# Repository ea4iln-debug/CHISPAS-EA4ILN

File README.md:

# Chispas EA4ILN

**Entrenador de telegrafía (CW) portátil para radioaficionados, basado en la Heltec WiFi LoRa 32 V3.**

> *"Chispas"* era el apodo que se daba al radiotelegrafista de a bordo.

> [!WARNING]
> **Desde la v1.10 Chispas ya no es beta**, pero sigue siendo un proyecto personal montado en placa perforada: la
> salida KEY se ha probado con dos transceptores y algunos valores del circuito son de partida. Úsalo bajo tu
> responsabilidad: lee el [descargo de responsabilidad](#descargo-de-responsabilidad).

<p align="center">
  
  <br>
  <sub>El prototipo en protoboard (12 de octubre de 2026): Heltec V3 con antena LoRa, encoder, buzzer, volumen,
  manipulador de palas, jacks de auriculares, de KEY y de audio de la emisora, optoacoplador y sensor BME280.</sub>
</p>

Chispas reúne en un aparato de bolsillo lo necesario para aprender y practicar CW: un entrenador por el método Koch,
un keyer iámbico, un modo de repetición (Echo), práctica en pareja y QSO por radio LoRa, conexión con el transceptor
(manipulación por KEY, tune, decodificador y memorias) y utilidades de estación, como la propagación, los spots POTA y
la línea gris. Todo se maneja con un encoder rotativo y una pantalla OLED, y se actualiza solo desde las releases de
GitHub.

---

## Índice

- [Funciones](#funciones)
- [Hardware](#hardware)
- [Conexiones](#conexiones)
- [Instalar el firmware](#instalar-el-firmware)
- [Actualizar por WiFi (OTA)](#actualizar-por-wifi-ota)
- [Manejo](#manejo)
- [Pantallas](#pantallas)
- [Configuración](#configuración)
- [Estructura del repositorio](#estructura-del-repositorio)
- [Detalles técnicos](#detalles-técnicos)
- [Hoja de ruta](#hoja-de-ruta)
- [Avisos](#avisos)
- [Descargo de responsabilidad](#descargo-de-responsabilidad)
- [Créditos y referencias](#créditos-y-referencias)
- [Licencia](#licencia)
- [Autor](#autor)

---

## Funciones

| Función | Descripción | Estado |
|---|---|---|
| **Koch (RX)** | Orden de caracteres de LCWO (lecciones 1–40), grupos aleatorios configurables (wpm, velocidad efectiva como en LCWO, caracteres y grupos), o **indicativos** al azar y **frases de QSO POTA**. La letra nueva de cada lección sale el 25 % de las veces y, con el **refuerzo**, las letras que más fallas salen más (hasta el doble o el triple). Al terminar se corrige **letra a letra** (marcando cada fallo) o con el **total de fallos**; estadísticas por lección y por carácter. | ✅ |
| **Echo (TX)** | Chispas emite letras y hay que repetirlas con las palas. Ajustes propios (wpm, velocidad efectiva, lección, letras por reto, número de retos, refuerzo de las letras con más errores), resultado al terminar y estadísticas por lección y por carácter. | ✅ |
| **TX libre (keyer iámbico)** | Modos A y B, 10–40 wpm, palas normales o invertidas. Descodifica en pantalla lo que se manipula y mide tu **ritmo** (espacios entre letras y palabras, titubeos, velocidad real) con un consejo. | ✅ |
| **QSO SIM** | Simulador de QSO POTA con las palas, en los dos papeles (ajuste **ROL**): de cazador (Chispas llama CQ; tú, indicativo, `5NN`, `73`) o de activador (llamas tú CQ y Chispas es el cazador: a veces da medio indicativo, vuelve a llamar si tardas o copia mal el tuyo). Si no te copia, te pide repetir. Velocidad y velocidad efectiva del activador, texto en pantalla y condiciones de banda: **QSB**, **ruido**, **estática de tormenta** y **QRM** (NO / SUAVE / FUERTE). | ✅ |
| **Práctica Duo por LoRa** | Práctica en pareja entre dos Chispas: uno envía grupos (o indicativos, o frases de QSO POTA) y el otro los recibe y los copia. Tramas digitales a 868 MHz, sin audio. | ✅ |
| **QSO libre por LoRa** | QSO con las palas entre dos Chispas: cada palabra se envía al terminarla y lo recibido suena cuando dejas de manipular (si manipulas mientras suena, se corta). | ✅ |
| **Transceptor (TRX)** | Manipulación de la emisora por KEY (aislada con optoacoplador), **tune** (portadora de 1–10 s), 6 memorias con variables (`{MI}`, `{SU}`, `{WX}`), decodificador CW del audio de la emisora (comprobado con audio Morse real) y QSO con las dos cosas a la vez (OPERAR para copiar de oído; QSO para que CHISPAS decodifique mientras transmites). | ✅ |
| **Propagación** | Índices solares y condiciones por banda de [hamqsl.com](https://www.hamqsl.com/). | ✅ |
| **Spots POTA** | Activaciones en CW publicadas en [pota.app](https://pota.app/). **Autospot** (beta): desde los parques cercanos, publicas tu propio spot (parque, indicativo, banda, frecuencia, QRP/QRT o un comentario propio) y CHISPAS te avisa a los 25 min para renovarlo. La **activación en curso** (duración, spots, botón de QRT) no se olvida aunque apagues. | ✅ |
| **Cluster** (beta) | Spots en vivo por telnet: el [RBN](https://reversebeacon.net/) (receptores automáticos de CW, con dB y WPM), el cluster de la [URE](https://www.ure.es/cluster-telnet-ea4ure/) (`ea4ure.com:7300`), VE7CC, WA9PIE o uno propio desde WEBCONF. Filtros de modo (TODOS/CW) y banda en CHISPAS, nunca en tu cuenta del cluster. Un spot por estación, con el mejor receptor y cuántos la oyen; "a SU" pasa su indicativo a TRX. **¿Quién me oye?**: los receptores del RBN que copian tu CQ, con la distancia exacta a cada uno; con **ESCUCHA EN TRX** (SI de serie) sigue escuchando el RBN mientras llamas CQ desde TRX › OPERAR o QSO (solo ahí se enciende el WiFi), y su `menu` lleva directo a la lista (y vuelve). | ✅ |
| **Sol y línea gris** | Salida y puesta del sol y ventanas de línea gris de hoy y de mañana, y altura actual del sol, para el locator de la estación. Funciona sin conexión. | ✅ |
| **Sensor ambiental (BME280)** | Temperatura, humedad y presión; tendencia de la presión en 3 h con **aviso de tormenta**; altitud barométrica calibrable (útil en SOTA); la temperatura en las memorias con `{WX}`. Opcional: sin sensor, Chispas funciona igual. | ✅ |
| **Configuración en el aparato** | Indicativo, locator, altitud, aceleración del encoder, apagado automático, tono y reset de fábrica, con el encoder. Página STATUS con estación, sistema, WiFi, memoria, arranque y sensor. | ✅ |
| **Configuración por WiFi** | Portal web en castellano, con QR para unirse desde el móvil: red, estación, hora y memorias. | ✅ |
| **Actualización OTA** | Busca la última release en GitHub, avisa si hay versión nueva y la instala por WiFi (TLS validado). | ✅ |
| **Batería** | Tensión y porcentaje. Detecta cuando no hay batería conectada. | ✅ |
| **Cara de Chispas** | Salvapantallas animado con expresiones y gestos, también de radioaficionado: antena llamando CQ, auriculares, bocadillo con CQ/73/88 y guiño en Morse. Reacciona a la línea gris, a la buena propagación y al aviso de tormenta. Sale tras el tiempo elegido sin uso en cualquier pantalla salvo CW, LoRa y TRX. | ✅ |
| **Tono por altavoz y auriculares** | Tono CW (400–1000 Hz, 850 por defecto) por un altavoz con amplificador PAM8302A, con volumen y silencio automático del altavoz al conectar auriculares. Audio sintetizado (sigma-delta a 16 kHz): tono sin clics y, en el simulador, ruido, estática, QRM y QSB. El amplificador solo se enciende en CW, LoRa y TRX. | ✅ |
| **Ahorro de energía** | CPU a 80 MHz sin WiFi, radio dormida fuera de LoRa, pantalla atenuada y apagado automático (deep sleep). | ✅ |
| **GPS** | Hora, locator y altitud automáticos (QNH del BME280 e historial de presión a nivel del mar). Duerme casi siempre para ahorrar. Opcional. | ✅ |

---

## Hardware

Resumen con fotos, fases del desarrollo, piezas, conexiones y la PCB (aún sin probar):
**[página de hardware](https://ea4iln-debug.github.io/CHISPAS-EA4ILN/hardware.html)**.

### Placa principal
- **[Heltec WiFi LoRa 32 V3](https://heltec.org/project/wifi-lora-32-v3/)**: ESP32-S3FN8 (8 MB de flash, sin PSRAM), radio
  LoRa SX1262 a 868 MHz, pantalla OLED de 0,96" (128×64, SSD1306) y cargador de batería LiPo integrado.

### Componentes del prototipo
El prototipo actual se monta en protoboard, sin PCB. Componentes principales:

- Encoder rotativo **KY-040** con pulsador.
- Manipulador de **palas** con clavija estéreo de 3,5 mm.
- Amplificador **PAM8302A** con **altavoz de 8 Ω**, potenciómetro de volumen de 10 kΩ logarítmico y jack de
  auriculares con conmutación (al meter la clavija, el altavoz calla). Sustituye al buzzer piezoeléctrico del
  principio, que a 3,3 V sonaba muy bajo.
- Optoacoplador **PC817** para la salida KEY, con resistencia de 10 kΩ a GND y un jack con la punta y el anillo
  unidos (vale para emisoras que manipulan por cualquiera de los dos).
- Entrada de audio de la emisora para el decodificador: polarización a 1,65 V, trimmer de nivel y diodos de protección.
- Módulo **GPS** NEO-6M (opcional): hora, locator y altitud. Se duerme por software entre lecturas.
- Batería **LiPo** de 3,7 V con conector JST de 1,25 mm. Comprueba la polaridad antes de conectarla.

El esquema completo (7 hojas), con la lista de componentes y el orden de montaje, está en
[`docs/esquema_protoboard.pdf`](docs/esquema_protoboard.pdf).

---

## Conexiones

| GPIO | Conector | Uso | Estado |
|---|---|---|---|
| 2 | J3-13 | Salida KEY (PC817, 330 Ω, y 10 kΩ a GND). Solo la activa la pantalla TRX | ✅ (probada con una uSDR y una Xiegu X6200) |
| 4 | J3-15 | Pala de punto (DIT), pull-up interno | ✅ |
| 5 | J3-16 | Pala de raya (DAH), pull-up interno | ✅ |
| 6 | J3-17 | Entrada de audio del decodificador (ADC1, por DMA) | ✅ |
| 7 | J3-18 | Tono CW por sigma-delta (amplificador con altavoz y auriculares) | ✅ |
| 38 | J3-11 | Apagado (SD) del amplificador PAM8302A: solo encendido en CW, LoRa y TRX | ✅ |
| 19 | J2-18 | Encoder CLK | ✅ |
| 20 | J2-17 | Pulsador del encoder (también despierta la placa) | ✅ |
| 48 | J2-14 | Encoder DT | ✅ |
| 47 | J2-13 | RX desde el TX del GPS | ✅ |
| 39 | J3-10 | TX al RX del GPS (órdenes UBX para dormirlo) | ✅ |
| 41 / 42 | J3-8 / J3-7 | I2C (Wire1) del sensor BME280 (opcional) | ✅ |

Notas:
- El pin 1 de cada conector es el de pad cuadrado, el más cercano al USB, y es GND. La alimentación de 3,3 V está en J3-2/3.
- Todos los módulos van a **3,3 V**. Los GPIO del ESP32-S3 no admiten 5 V.
- GPIO19 y GPIO20 son las líneas USB D−/D+ del S3, pero funcionan como entradas porque la V3 programa a través de un
  conversor CP2102 (probado en placa). En Windows hace falta el driver
  [CP210x de Silicon Labs](https://www.silabs.com/developers/usb-to-uart-bridge-vcp-drivers).

---

## Instalar el firmware

El firmware es para la placa con **encoder**. Hasta la v1.10 hubo también una compilación `sin-encoder`, para una
placa desnuda que se manejaba solo con el botón PRG; desde la 1.20 ya no existe (una placa sin encoder se queda en la
v1.10; el OTA dirá que no hay binario para ella).

### Desde el navegador (lo más fácil)
Abre **[ea4iln-debug.github.io/CHISPAS-EA4ILN](https://ea4iln-debug.github.io/CHISPAS-EA4ILN/)** con Chrome o Edge
en un ordenador, conecta la placa por USB y pulsa **Instalar en la placa**. Instala la última versión estable o,
si hay una más nueva, la **beta** (selector encima del botón), y **conserva la configuración** guardada, salvo que marques borrar la placa (recomendable si traía otro firmware).
En Windows hace falta el driver del CP210x (ver arriba).

### Sin compilar (desde la release)
En [Releases](https://github.com/ea4iln-debug/CHISPAS-EA4ILN/releases) están las imágenes listas:

| Archivo | Para qué |
|---|---|
| `chispas-<versión>-usb.bin` | Primera instalación por USB (imagen completa, se graba en `0x0`) |
| `chispas-<versión>.bin` | Solo la aplicación: la usa la actualización OTA |

Para grabar la imagen completa basta con [ESP Tool web](https://espressif.github.io/esptool-js/) (en Chrome o Edge:
*Connect*, dirección `0x0`, el archivo `-usb.bin` y *Program*) o, con Python:

```bash
pip install esptool
esptool.py --chip esp32s3 --port COMx write_flash 0x0 chispas-1.03b-usb.bin
```

La imagen completa **borra la configuración** guardada (estación, estadísticas y red WiFi): úsala para la primera
instalación. Para las siguientes versiones, usa la [actualización por WiFi](#actualizar-por-wifi-ota), que lo conserva.

### Compilando (PlatformIO)
- [Visual Studio Code](https://code.visualstudio.com/) con la extensión [PlatformIO IDE](https://platformio.org/), o
  la línea de órdenes de PlatformIO (`pio`).
- Cable USB-C con datos.

Las dependencias se instalan solas al compilar. Están fijadas en [`platformio.ini`](platformio.ini):

| Componente | Versión |
|---|---|
| Plataforma `espressif32` (core Arduino 2.0.17) | 6.13.0 |
| [RadioLib](https://github.com/jgromes/RadioLib) | ^6.6 |
| [Adafruit GFX](https://github.com/adafruit/Adafruit-GFX-Library) y [SSD1306](https://github.com/adafruit/Adafruit_SSD1306) | ^1.11 / ^2.5 |
| [WiFiManager](https://github.com/tzapu/WiFiManager) | ^2.0.17 |
| [ArduinoJson](https://arduinojson.org/) | ^7.2 |

```bash
git clone https://github.com/ea4iln-debug/CHISPAS-EA4ILN.git
cd CHISPAS-EA4ILN
pio run                                         # compila el firmware
pio run -t upload --upload-port COMx            # lo carga (en Linux/macOS, /dev/ttyUSB0 o similar)
pio device monitor                              # monitor serie a 115200 baudios
```

### Programas de prueba
En [`pruebas/`](pruebas/) hay programas independientes para comprobar el hardware sin tocar el firmware:

| Entorno | Para qué |
|---|---|
| `pio run -e prueba_pines -t upload` | Comprueba los pines del encoder e imprime por serie cada cambio y el sentido de giro |
| `pio run -e prueba_bateria -t upload` | Mide la lectura de batería (media y dispersión) con y sin batería conectada |

Después de usarlos, vuelve a cargar el firmware con `pio run -t upload`.

---

## Actualizar por WiFi (OTA)

Con una red WiFi guardada (ver [Configuración](#configuración)):

1. Ve a **CONF. > CONFIG > ACTUALIZAR FW**. Chispas se conecta, consulta la última release de este repositorio
   (también las beta) y la compara con la instalada.
2. Si hay una más nueva, la enseña (`NUEVA v1.01b`) y pide confirmar con **instalar**. Descarga el binario de su
   placa, lo instala en la otra partición de la flash y reinicia. Si algo falla, la versión
   instalada sigue intacta.
3. Además, cuando Chispas enciende el WiFi en PROP. o POTA, mira una vez al día si hay versión nueva y lo
   avisa en el menú (`FW NUEVO: v1.01b`).
4. Si la descarga se queda parada 30 s, Chispas se reinicia y sigue con la versión que tenía.

Con batería por debajo del 30 % (y sin USB) no instala, para que no se quede a medias. La conexión con GitHub va
cifrada y se comprueba con los certificados raíz de [`include/certificados_github.h`](include/certificados_github.h).

---

## Manejo

Todo se hace con el **encoder**:

| Acción | Efecto |
|---|---|
| **Girar** | Mueve el foco por las opciones, incluidas las flechas `ant.` y `sig.` para cambiar de pantalla; en las páginas de datos, pasa de página |
| **Pulsar** | Ejecuta la opción con el foco |
| **Pulsar sobre un valor** | Entra en edición (el valor sale en vídeo inverso): girar lo cambia y pulsar otra vez lo confirma. Al girar rápido, los valores largos avanzan de varios en varios (aceleración, ajustable en CONFIG) |
| **Pulsación larga** | Atajo en algunas pantallas, como salir de la práctica o repetir |
| **Botón PRG** (corto) | *Atrás*: sale de la edición o del submenú y, en las pantallas principales, vuelve a Inicio |
| **Botón PRG** (largo) | Duerme Chispas (deep sleep); se despierta pulsando PRG o el eje del encoder |

Todas las pantallas siguen el mismo esquema:
- **Menú:** título en negativo, opciones `< ... >` y `ant.`/`sig.` abajo.
- **Ajustes:** lista con el nombre a la izquierda y el valor a la derecha (4 a la vista, con barra de desplazamiento),
  y las acciones en el pie (`volver`, o `iniciar` y `volver`).
- **Datos en páginas:** se pasan girando; el pie dice la página (`1/2 INDICES`) y pulsar vuelve.
- **Pantallas de manipular o escuchar** (TX libre, Operar, QSO, Duo, Decodificar): pie corto con lo que se usa sin
  soltar las palas y **menu** para el resto de ajustes.

Al cambiar de pantalla, el foco se queda en la flecha que has usado, así que basta con pulsar varias veces seguidas
para recorrer las pantallas en un sentido.

Sin encoder (compilación `sin-encoder`, solo hasta la v1.10), todo se hace con el botón PRG: corta = mover el foco, larga = ejecutar y
muy larga (2,5 s) = dormir.

---

## Pantallas

| N.º | Pantalla | Contenido |
|---|---|---|
| 1 | **Inicio** | Nombre, indicativo y versión. Tras unos segundos sin uso aparece la cara de Chispas (también en PROP., POTA, SOL, TIEMPO y CONF.). |
| 2 | **CW** | Entrenador: `KOCH (RX)`, `ECHO (TX)`, `QSO SIM` (simulador de QSO POTA) y `tx libre` en el pie (keyer), con ajustes, práctica y estadísticas |
| 3 | **LoRa** | `PRÁCTICA DUO` (grupos en pareja) y `QSO LIBRE` (con las palas) |
| 4 | **TRX** | Transceptor: `DECODIFICAR` (solo recibe), `OPERAR` (transmitir por KEY, con memorias y tune, copiando de oído), `QSO` (OPERAR con el decodificador a la vez) y `memorias` |
| 5 | **PROP.** | Propagación: índices solares y condiciones por banda |
| 6 | **POTA** | Spots de activaciones en CW, parques POTA más cercanos (con el GPS o el locator) y autospot desde un parque |
| 7 | **CLUSTER** (`DXC` en la cabecera) | Spots en vivo por telnet del RBN (por defecto), del cluster de la URE u otros, con filtros de modo y banda; ficha del spot y "a SU" (pasa el indicativo a TRX); `QUIÉN ME OYE?`: los receptores del RBN que te copian, del más lejano al más cercano, con km y dB. Necesita tu indicativo y WiFi |
| 8 | **SOL** | Sol y línea gris: hoy, ahora y mañana |
| 9 | **TIEMPO** (`WX` en la cabecera) | Tiempo de [Open-Meteo](https://open-meteo.com/) (CC BY 4.0) para el locator o el GPS: ahora, próximas 12 h cada 3 h y mañana; con el BME280, también AMBIENTE |
| 10 | **CONF.** | `CONFIG` (estación, encoder, apagado, tono, webconf, actualización, depuración y fábrica) y `STATUS` |

La cabecera muestra la hora (local o UTC, a elegir), una `W` si el WiFi está encendido y una `L` si la radio LoRa
está escuchando (Práctica Duo y QSO libre), ambas en negativo, el nombre de la pantalla y la batería (`PWR` si no hay
batería).
Las capturas salen de la propia pantalla con [`docs/captura_oled.py`](docs/captura_oled.py) (necesita
**CONF. > CONFIG > DEPURACION > ORDENES SERIE** en `SI`).

### Entrenador CW

| | | |
|:---:|:---:|:---:|
| <br>Menú | <br>Koch: ajustes | <br>Koch: práctica |
| <br>Koch: grupos emitidos | <br>Koch: corregir con el total | <br>Koch: más errores |
| <br>Koch: totales | <br>Koch: lecciones | <br>Echo: ajustes |
| <br>Echo: práctica | <br>Echo: más errores | <br>Echo: lecciones |
| <br>TX libre (keyer) | <br>TX libre: menu | <br>QSO SIM: ajustes |

### LoRa

| | | |
|:---:|:---:|:---:|
| <br>Menú | <br>Práctica Duo | <br>Duo: menu |
| <br>QSO libre | <br>QSO libre: menu | |

### Transceptor (TRX)

| | | |
|:---:|:---:|:---:|
| <br>Menú | <br>Operar | <br>Operar y QSO: menu |
| <br>QSO | <br>Decodificar (sin señal) | <br>Memorias |
| <br>Editor (rueda de caracteres, con {WX}) | | |

### Cluster

| | | |
|:---:|:---:|:---:|
| <br>Menú | <br>Spots (RBN) | <br>Ficha y "a SU" |
| <br>¿Quién me oye? (tras un CQ en 20 m) | <br>Ajustes: nodo, modo, banda y escucha en TRX | <br>Volver, detrás del último spot |

### Utilidades

| | | |
|:---:|:---:|:---:|
| <br>Propagación: menú | <br>Índices | <br>Condiciones por banda |
| <br>POTA: menú | <br>Spots POTA | <br>Sol: menú |
| <br>Sol: hoy | <br>Sol: ahora | <br>Sol: mañana |
| <br>Tiempo: ahora | <br>Tiempo: horas | <br>Tiempo: mañana |
| <br>Ambiente (BME280) | <br>POTA: parques cercanos | <br>POTA: spot desde un parque |
| <br>Autospot: ficha | <br>Autospot: activación en curso | <br>Inicio: activando |

### Configuración

| | | |
|:---:|:---:|:---:|
| <br>Menú | <br>CONFIG | <br>CONFIG (sigue) |
| <br>Editor del indicativo | <br>STATUS: estación | <br>STATUS: sistema |
| <br>STATUS: WiFi | <br>STATUS: memoria | <br>STATUS: arranque |
| <br>Webconf | <br>QR para unir el móvil | <br>Actualizar firmware |
| <br>STATUS: sensor | <br>CONFIG (sigue) | <br>Depuración |
| <br>Poner hora (RELOJ) | <br>STATUS: GPS (sin fijo) | |

---

## Configuración

### En el aparato
**CONF. > CONFIG** reúne los ajustes generales:

| Opción | Qué hace |
|---|---|
| **ID** | Tu indicativo (3 a 8 letras, cifras y `/`), con la rueda de caracteres del editor. De fábrica, `EAXXXX`: con él no se abren OPERAR y QSO de TRX ni el autospot (aviso con `config`, que lleva al editor) |
| **LOCATOR** | Locator Maidenhead de 4 o 6 caracteres (para SOL); se comprueba al guardar. Con GPS: pulsar, girar entre `AUTO (GPS)` y `MANUAL` y pulsar (MANUAL abre el editor) |
| **ALTITUD** | Con el BME280: altitud barométrica (con `?` si no está calibrada). Pulsar, girar hasta la altitud real y pulsar calibra el QNH (con GPS se calibra solo) |
| **HORA** | Hora de la cabecera: `LOCAL` o `UTC` (`12:05Z`) |
| **RELOJ** | De dónde viene la hora: `GPS`, `WIFI`, `MANUAL` o `SIN HORA`; si hay varias, se queda la más exacta. Pulsar abre **PONER HORA**: girar cambia el campo, pulsar pasa al siguiente y, en el año, la pone |
| **TONO** | Frecuencia del tono CW (400–1000 Hz), con un pitido de prueba |
| **ACELERACION** | Salto de los valores al girar rápido: `NO` o x2 a x5 |
| **SALVAPANTALLAS** | Tiempo sin uso antes de que salga la cara: `NO`, 15 s, 30 s, 1, 2 o 5 min |
| **APAGADO** | Minutos sin uso antes de dormir: nunca, 5, 10, 15, 30, 60 o 120 (nunca en CW, LoRa ni TRX) |
| **WIFI DATOS** | `MANUAL` (por defecto): PROP., POTA, SOL y TIEMPO solo encienden el WiFi al pulsar **ACTUALIZAR** (`CONECTANDO WIFI...`, `DESCARGANDO...`; mientras conecta, **cancelar**) y lo apagan al terminar; los datos se quedan hasta la siguiente vez (en los spots, su antigüedad en el pie). `AUTO`: se conecta al entrar en esas pantallas y refresca solo (POTA cada 2 min, PROP. cada hora) |
| **WEBCONF** | Abre el portal WiFi (ver abajo) |
| **ACTUALIZAR FW** | Actualización por OTA (ver [arriba](#actualizar-por-wifi-ota)) |
| **DEPURACION** | Mensajes y órdenes por serie para pruebas: órdenes serie, diagnóstico, decodificador y retraso CW (todo en `NO` por defecto) |
| **FABRICA** | Borra todo (pide confirmar) y reinicia |

**CONF. > STATUS** muestra, en siete páginas, la estación (ID, locator, hora y versión), el sistema (batería, LoRa,
apagado, tono y aceleración), el WiFi (red guardada, estado, IP y nombre del portal), la memoria, el arranque
(tiempo encendido y motivo del último reinicio), el sensor ambiental (chip, QNH e historial) y el GPS (estado,
satélites, posición, altitud, HDOP, locator y antigüedad del dato; mientras se ve, el GPS está despierto).

### Por WiFi (webconf)
Chispas solo enciende el WiFi cuando lo necesita: en PROP. y POTA, en SOL si aún no tiene hora, para el portal y
para actualizar. La red WiFi, la hora y las memorias se configuran desde el móvil:

1. Ve a **CONF. > CONFIG > WEBCONF** y pulsa. Chispas crea la red `Chispas-XXXX` (clave `chispas73`) y muestra los
   datos en pantalla.
2. Únete a esa red. Con la opción **ver qr** aparece un QR que el móvil escanea para unirse directamente.
3. Si la página no se abre sola, entra en **http://192.168.4.1**.
4. En **Red WiFi** eliges tu red y en **Estación, hora y memorias** pones el indicativo, el locator, la hora (formato
   `HH:MM DD-MM-AAAA`), si quieres la hora UTC en la cabecera y las 6 memorias de la pantalla TRX (`{MI}` = tu
   indicativo, `{SU}` = el del corresponsal, `{WX}` = la temperatura, p. ej. `WX 18C`, si hay BME280).

Si en PROP., POTA o SOL no hay red guardada o no conecta, Chispas no abre el portal por su cuenta: su menú ofrece
**ABRIR WEBCONF** y **REINTENTAR**.

> La clave del portal está definida en `PORTAL_CLAVE`, en `src/parts/wifi.inc`. Cámbiala si vas a usar Chispas en un lugar público.

---

## Estructura del repositorio

```
├── src/
│   ├── main.cpp                    Firmware: cabecera, setup y loop; incluye las partes en orden
│   └── parts/*.inc                 Resto del firmware por áreas (keyer, LoRa, TRX, WiFi, pantallas…)
├── include/
│   ├── wm_strings_chispas.h        Textos del portal WiFiManager en castellano
│   └── certificados_github.h       Certificados raíz para la actualización OTA
├── pruebas/                        Programas de prueba del hardware (entornos aparte)
├── compilar.sh                     Compila los dos entornos y resume errores, avisos, RAM y flash
├── docs/
│   ├── esquema_protoboard.pdf      Esquema de conexiones del prototipo (7 hojas)
│   ├── gen_esquema.py              Generador del esquema (HTML/SVG → PDF)
│   ├── captura_oled.py             Captura de la pantalla por serie (PNG)
│   ├── LICENCIAS_TERCEROS.txt      Avisos de licencia de las librerías incluidas en el firmware
│   ├── NOTAS.md                    Notas de desarrollo detalladas: historial de pruebas y decisiones
│   └── img/                        Capturas de las pantallas y foto del prototipo
├── platformio.ini                  Configuración de PlatformIO y dependencias
├── LICENSE                         Licencia del software (GPL-3.0)
├── LICENSE-HARDWARE.md             Licencia del hardware y la documentación (CC BY-NC-SA 4.0)
└── CLAUDE.md                       Resumen de desarrollo: estado, decisiones y pendientes
```

---

## Detalles técnicos

- **Temporización CW en tareas FreeRTOS.** La emisión (motor CW) y el keyer corren en tareas de mayor prioridad que
  el bucle principal, con plazos absolutos sobre ticks de 1 ms. La pantalla, la radio o el WiFi no alteran el ritmo
  del Morse (retraso medido: 0 ms).
- **Encoder por interrupción**, con decodificador de cuadratura por tabla que filtra los rebotes y medida del tiempo
  entre pasos para la aceleración.
- **LoRa con tramas digitales**, no audio: un byte por carácter (bit centinela; punto = 0, raya = 1), cabecera
  con tipo (grupo Duo o palabra de QSO), número de secuencia, wpm e indicativo. Antes de transmitir se escucha el
  canal (CAD).
- **Decodificador CW:** el ADC lee el audio de la emisora por DMA a 8 kHz en una tarea del otro núcleo; algoritmo de
  Goertzel en bloques de 12 ms, tono fijo o automático (400–1000 Hz), umbral y velocidad adaptativos, silenciador
  (con solo ruido de banda no descodifica) y fin de palabra según la pausa real entre letras. No escucha mientras se
  emite por KEY. Comprobado con audio Morse real.
- **Salida KEY con seguridad:** solo se activa en la pantalla TRX y se corta sola si queda activa más de 10 s (en el
  tune, su duración más 2 s).
- **Actualización OTA:** consulta la API de GitHub, compara versiones (`1.00b` < `1.01b` < `1.01`) y escribe la otra
  partición de aplicación (`default_8MB.csv`: dos de 3,2 MB). TLS validado con certificados raíz incluidos.
- **Radio:** 868,1 MHz, SF7, 250 kHz, CR 4/7, 10 dBm.
- **Detección de batería ausente:** con USB y sin batería, el cargador de la V3 deja una tensión media similar a la de
  una batería llena, pero oscila. Chispas mide la dispersión de una ráfaga de lecturas para distinguir los dos casos.
- **QR de WiFi** generado con el componente `qrcode` de ESP-IDF incluido en el core, sin librerías adicionales.
- **Cálculo solar** con las ecuaciones de la NOAA a partir del locator Maidenhead.
- **Persistencia** en NVS: configuración del entrenador, keyer, Echo y TRX, estadísticas, datos de la estación y
  memorias.
- **Depuración:** en **CONF. > CONFIG > DEPURACION** se activan, sin recompilar, las órdenes por serie (captura
  de pantalla y simulación del encoder) y los mensajes `[DIAG]`, `[DECOD]` y `[CW]`; se guardan en NVS.

---

## Hoja de ruta

Lo pendiente (pruebas, hardware y desarrollo) está en [ROADMAP.md](ROADMAP.md). Lo siguiente: cola de spots POTA
y la PCB.

---

## Avisos

- **LoRa a 868 MHz:** Chispas transmite en la banda ISM de 868 MHz (sub-banda 868,0–868,6 MHz, 25 mW, ciclo de
  trabajo del 1 %). Respeta la normativa de tu país.
- **Salida KEY:** manipular un transceptor de radioaficionado requiere la licencia correspondiente.
- **SOTA:** no hay cliente de SOTA. Las condiciones de su API exigen aprobación previa para software de terceros
  como este.
- **Servicios externos:** los datos de propagación y de POTA vienen de servicios públicos. hamqsl.com pide no consultar
  su XML más de una vez por hora y Chispas lo respeta. pota.app no publica condiciones para su API: Chispas la consulta
  cada 2 minutos, solo con la pantalla POTA abierta, y descarga la lista de parques de España como mucho una vez al mes. La API de GitHub se consulta al pedir la actualización y, como
  mucho, una vez al día para el aviso.

---

## Descargo de responsabilidad

Chispas es un proyecto personal de radioafición, sin ánimo de lucro. Se ofrece **tal cual, sin
garantía de ningún tipo**: ni de que funcione, ni de que sirva para un fin concreto, ni de que esté libre de errores
(ver las licencias GPL-3.0 y CC BY-NC-SA 4.0).

- **Responsabilidad:** quien monte, modifique o use Chispas lo hace bajo su propia responsabilidad. El autor no
  responde de daños en personas, en la placa, en el transceptor o en otros equipos, ni de pérdidas de datos o de
  cualquier otro perjuicio derivado de su uso.
- **Circuitos:** los esquemas y valores son de un prototipo y en buena parte no se han probado en banco. Revísalos
  antes de montarlos y comprueba con el polímetro antes de conectar nada.
- **Transceptor:** conectar Chispas a una emisora (salida KEY y entrada de audio) puede dañar uno u otro equipo si se
  monta mal. Usa siempre el aislamiento previsto (optoacoplador) y prueba primero sin la emisora. La salida KEY tiene
  un corte de seguridad por software, pero no sustituye a la vigilancia del operador.
- **Batería LiPo:** una batería mal conectada, dañada o cargada sin vigilancia puede calentarse o incendiarse.
  Comprueba la polaridad y no la dejes cargando desatendida.
- **Actualizaciones:** no apagues Chispas mientras instala una versión. Si algo sale mal, se puede volver a grabar
  siempre por USB.
- **Normativa:** la emisión por LoRa (868 MHz) y la manipulación de un transceptor de radioaficionado están sujetas a
  la normativa de cada país y, en el segundo caso, a tener la licencia correspondiente. Cumplirla es cosa de quien
  opera el equipo.
- **Servicios externos:** los datos de propagación y de POTA vienen de servicios de terceros que pueden cambiar o
  dejar de funcionar; no deben usarse para decisiones críticas.

---

## Créditos y referencias

- Método Koch y orden de caracteres de [LCWO.net](https://lcwo.net/) (Fabian Kurz, DJ5CW).
- [Morserino-32](https://www.morserino.info/), como referencia de diseño (no se ha copiado código).
- [Meshtastic](https://meshtastic.org/), como referencia de datos de la Heltec V3 (tensión del TCXO, lectura de la
  batería); no se ha copiado código.
- Datos de propagación: [HAMQSL.com](https://www.hamqsl.com/), de Paul L. Herrman, N0NBH, y las fuentes que él cita.
  Spots: [pota.app](https://pota.app/) (Parks on the Air).
- Cálculo solar con las ecuaciones de la [NOAA](https://gml.noaa.gov/grad/solcalc/calcdetails.html) (dominio
  público).
- Librerías:

  | Librería | Licencia |
  |---|---|
  | [Arduino-ESP32](https://github.com/espressif/arduino-esp32) (core) | LGPL-2.1 |
  | [ESP-IDF](https://github.com/espressif/esp-idf), incluido en el core (ADC por DMA, `qrcode`, mbedTLS) | Apache-2.0 |
  | [QR Code generator](https://www.nayuki.io/page/qr-code-generator-library) (Project Nayuki), dentro del `qrcode` de ESP-IDF | MIT |
  | [RadioLib](https://github.com/jgromes/RadioLib) | MIT |
  | [Adafruit GFX](https://github.com/adafruit/Adafruit-GFX-Library) y [Adafruit SSD1306](https://github.com/adafruit/Adafruit_SSD1306) | BSD |
  | [Adafruit BusIO](https://github.com/adafruit/Adafruit_BusIO) | MIT |
  | [WiFiManager](https://github.com/tzapu/WiFiManager) (la traducción de `include/wm_strings_chispas.h` parte de su archivo en español) | MIT |
  | [ArduinoJson](https://arduinojson.org/) | MIT |

---

## Licencia

Chispas tiene dos licencias, según el tipo de contenido:

| Parte | Licencia | Archivo |
|---|---|---|
| **Software**: firmware (`src/`), programas de prueba (`pruebas/`), `include/` y scripts (`docs/*.py`) | [GNU GPL v3.0 o posterior](https://www.gnu.org/licenses/gpl-3.0.html) | [`LICENSE`](LICENSE) |
| **Hardware y documentación**: esquema, lista de componentes, diseño del montaje, README e imágenes | [CC BY-NC-SA 4.0](https://creativecommons.org/licenses/by-nc-sa/4.0/deed.es) | [`LICENSE-HARDWARE.md`](LICENSE-HARDWARE.md) |

- **Software (GPL-3.0):** es software libre. Puedes usarlo, estudiarlo, modificarlo y redistribuirlo; si distribuyes
  el firmware o una versión modificada, debes hacerlo con la misma licencia y entregar el código fuente.
- **Hardware y documentación (CC BY-NC-SA 4.0):** puedes compartirlos y adaptarlos citando al autor, **sin fines
  comerciales** y con la misma licencia. Para un uso comercial, contacta con el autor.

`include/wm_strings_chispas.h` deriva de WiFiManager y conserva su aviso de licencia MIT. Las librerías externas
mantienen sus propias licencias (ver [Créditos y referencias](#créditos-y-referencias)); todas son compatibles con la
GPL-3.0. El repositorio solo contiene código fuente: PlatformIO descarga las librerías al compilar. Los binarios de las
releases van acompañados de [`docs/LICENCIAS_TERCEROS.txt`](docs/LICENCIAS_TERCEROS.txt), con los avisos de licencia
de las librerías que incluyen.

Las capturas de `docs/img/` muestran datos de terceros (propagación de HAMQSL.com y spots de pota.app), que siguen
siendo de sus autores.

---

## Autor

**EA4ILN**. Proyecto personal de radioafición. 73!

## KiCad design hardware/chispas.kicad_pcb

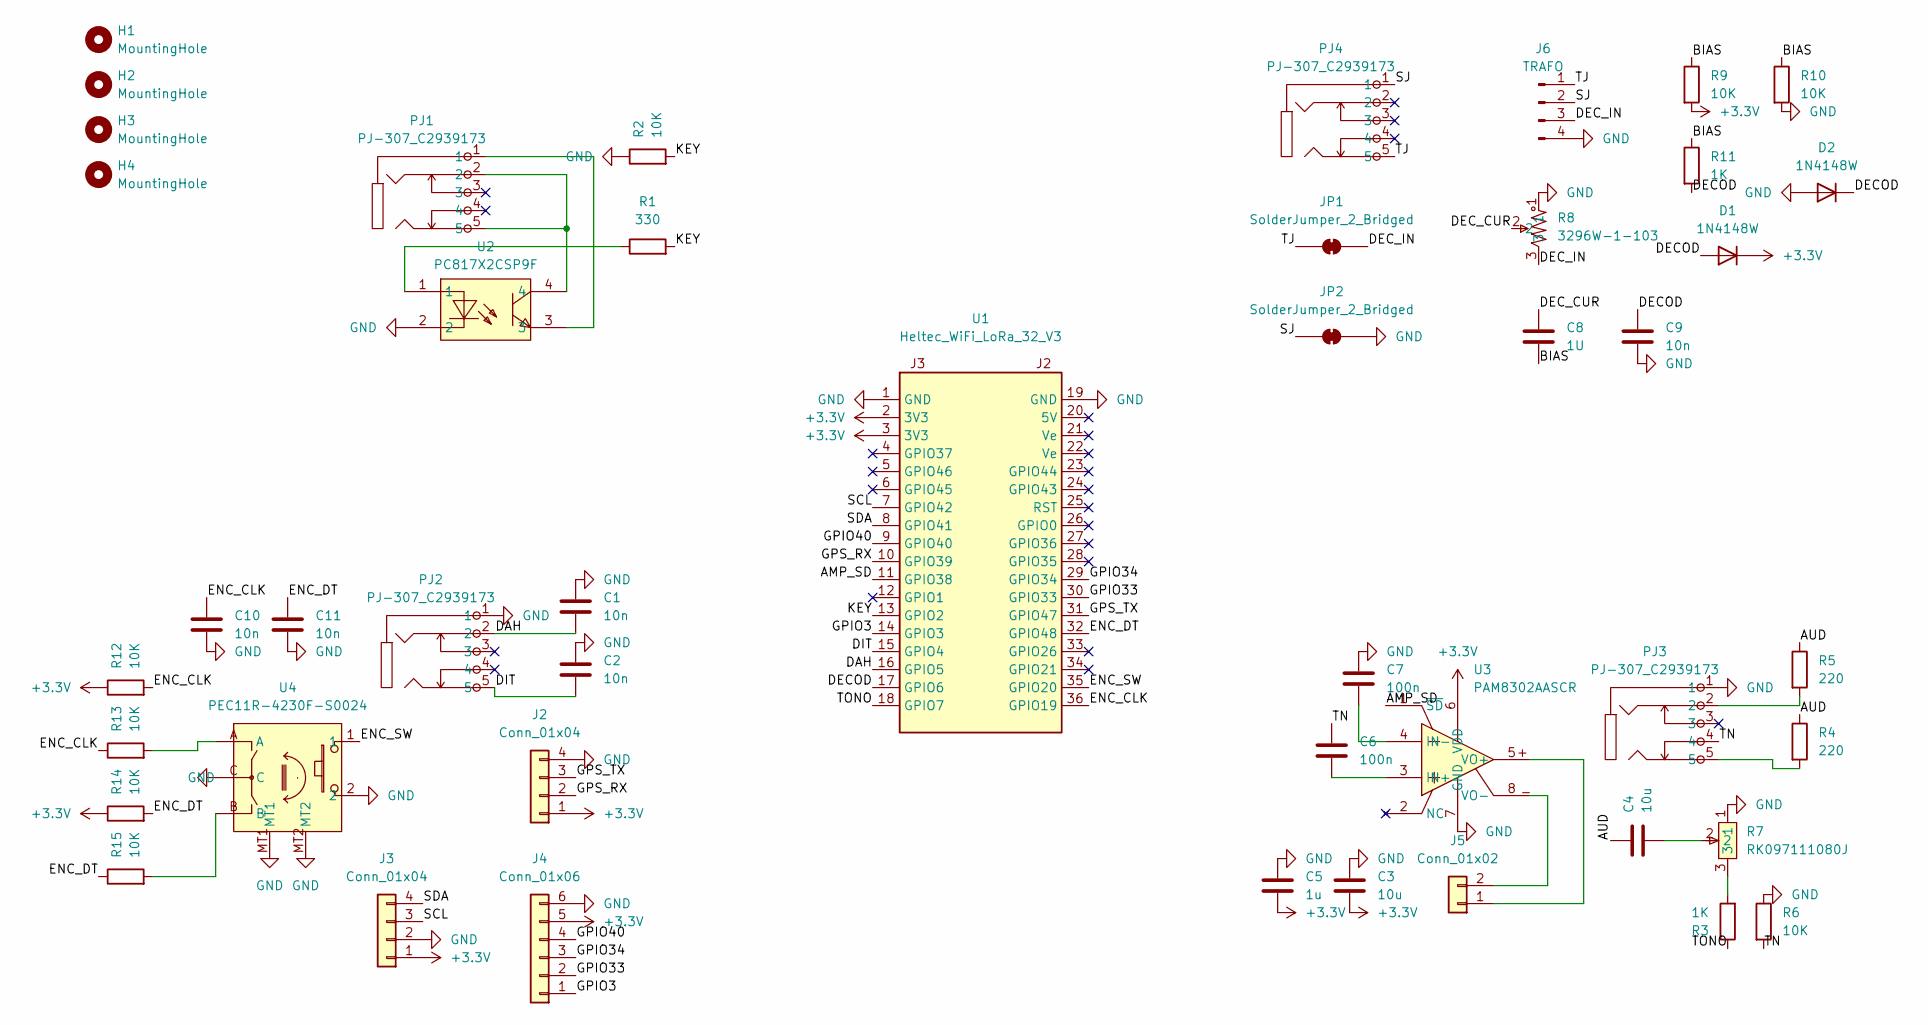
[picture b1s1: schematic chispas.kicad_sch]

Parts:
C1, C2, C9, C10, C11: 10n; C_0805_2012Metric; LCSC Part C1710
C3, C4: 10u; C_0805_2012Metric; LCSC Part C15850
C5: 1u; C_0805_2012Metric; LCSC Part C28323
C6, C7: 100n; C_0805_2012Metric; LCSC Part C49678
C8: 1U; C_0805_2012Metric; LCSC Part C28323
D1, D2: 1N4148W; D_SOD-123; LCSC Part C81598
H1, H2, H3, H4: MountingHole; MountingHole_3.2mm_M3
J2, J3: Conn_01x04; JST_XH_B4B-XH-A_1x04_P2.50mm_Vertical; LCSC Part C144395
J4: Conn_01x06; PinHeader_1x06_P2.54mm_Vertical
J5: Conn_01x02; JST_PH_B2B-PH-K_1x02_P2.00mm_Vertical; LCSC Part C131337
J6: TRAFO; PinHeader_1x04_P2.54mm_Vertical
JP1, JP2: SolderJumper_2_Bridged; SolderJumper-2_P1.3mm_Bridged_RoundedPad1.0x1.5mm
PJ1, PJ2, PJ3, PJ4: PJ-307_C2939173; AUDIO-TH_PJ-307; MPN PJ-307; LCSC Part C2939173
R1: 330; R_0805_2012Metric; LCSC Part C17630
R2, R6, R9, R10, R12, R13, R14, R15: 10K; R_0805_2012Metric; LCSC Part C17414
R3, R11: 1K; R_0805_2012Metric; LCSC Part C17513
R4, R5: 220; R_0805_2012Metric; LCSC Part C17557
R7: RK097111080J; RES-ADJ-TH_RK097111080J; MPN R09710NS-FB15D7.0-B103-0044; LCSC Part C18213426
R8: 3296W-1-103; RES-ADJ-TH_3P-L10.0-W10.0-P2.50-L; MPN 3296W-1-103; LCSC Part C118954
U1: Heltec_WiFi_LoRa_32_V3
U2: PC817X2CSP9F; SMD-4_L4.6-W6.5-P2.54-LS10.2-TL; MPN PC817X2CSP9F; LCSC Part C66405
U3: PAM8302AASCR; MSOP-8_L3.0-W3.0-P0.65-LS5.0-BL; MPN PAM8302AASCR; LCSC Part C113367
U4: PEC11R-4230F-S0024; SW-TH_PEC11R-4XXXF-SXXXX; MPN PEC11R-4230F-S0024; LCSC Part C7435302

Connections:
+3.3V: C3.2, C5.2, D1.1 (K), J2.1, J3.1, J4.5, R9.2, R12.1, R14.1, U1.2 (3V3), U1.3 (3V3), U3.6 (VDD)
/AMP_SD: U1.11 (GPIO38), U3.1 (~SD)
/AUD: C4.1, R4.1, R5.1
/BIAS: C8.2, R9.1, R10.1, R11.1
/DAH: C1.2, PJ2.2, U1.16 (GPIO5)
/DECOD: C9.1, D1.2 (A), D2.1 (K), R11.2, U1.17 (GPIO6)
/DEC_CUR: C8.1, R8.2
/DEC_IN: J6.3, JP1.2 (B), R8.3
/DIT: C2.2, PJ2.5, U1.15 (GPIO4)
/ENC_CLK: C10.1, R12.2, R13.1, U1.36 (GPIO19)
/ENC_DT: C11.1, R14.2, R15.1, U1.32 (GPIO48)
/ENC_SW: U1.35 (GPIO20), U4.1
/GPIO3: J4.1, U1.14 (GPIO3)
/GPIO33: J4.2, U1.30 (GPIO33)
/GPIO34: J4.3, U1.29 (GPIO34)
/GPIO40: J4.4, U1.9 (GPIO40)
/GPS_RX: J2.2, U1.10 (GPIO39)
/GPS_TX: J2.3, U1.31 (GPIO47)
/KEY: R1.2, R2.2, U1.13 (GPIO2)
/SCL: J3.3, U1.7 (GPIO42)
/SDA: J3.4, U1.8 (GPIO41)
/SJ: J6.2, JP2.1 (A), PJ4.1
/TJ: J6.1, JP1.1 (A), PJ4.5
/TN: C6.1, PJ3.4, R6.2
/TONO: R3.1, U1.18 (GPIO7)
GND: C1.1, C2.1, C3.1, C5.1, C7.1, C9.2, C10.2, C11.2, D2.2 (A), J2.4, J3.2, J4.6, J6.4, JP2.2 (B), PJ2.1, PJ3.1, R2.1, R6.1, R7.1, R8.1, R10.2, U1.1 (GND), U1.19 (GND), U2.2, U3.7 (GND), U4.2, U4.C, U4.MT1, U4.MT2
unnamed: C4.2, R7.2
unnamed: J5.1, U3.5 (VO+)
unnamed: J5.2, U3.8 (VO-)
unnamed: PJ1.1, U2.3
unnamed: PJ1.2, PJ1.5, U2.4
unnamed: PJ3.2, R5.2
unnamed: PJ3.5, R4.2
unnamed: R1.1, U2.1
unnamed: R3.2, R7.3
unnamed: R13.2, U4.A
unnamed: R15.2, U4.B
unnamed: C6.2, U3.3 (IN+)
unnamed: C7.2, U3.4 (IN-)

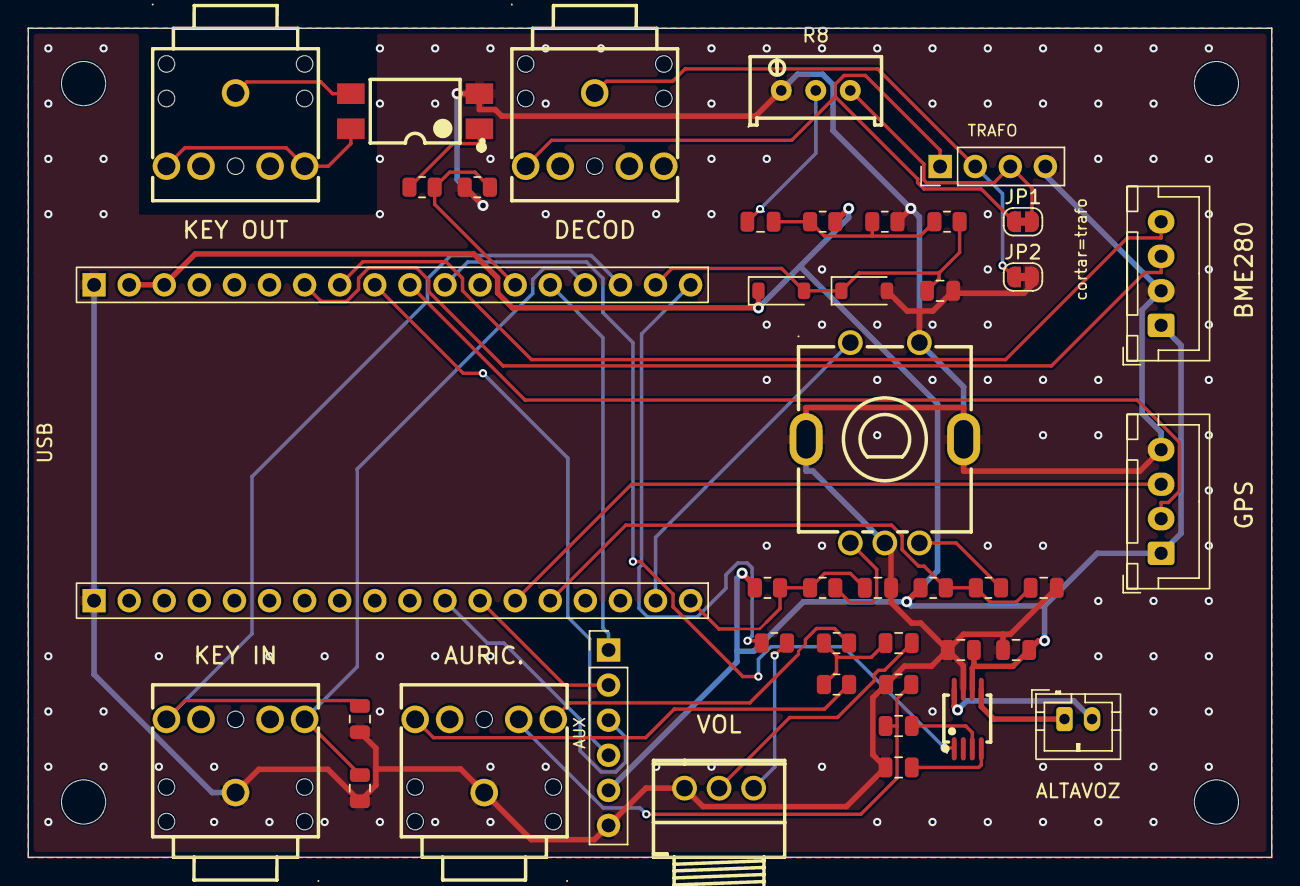
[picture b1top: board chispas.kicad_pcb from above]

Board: 2 copper layers, 90.0 x 60.0 mm, 47 parts (0 on the bottom side), 39 nets.

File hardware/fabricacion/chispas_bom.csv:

Comment,Designator,Footprint,LCSC
10n,"C1,C2,C9,C10,C11",C_0805_2012Metric,C1710
10u,"C3,C4",C_0805_2012Metric,C15850
1u,"C5,C8",C_0805_2012Metric,C28323
100n,"C6,C7",C_0805_2012Metric,C49678
1N4148W,"D1,D2",D_SOD-123,C81598
330,R1,R_0805_2012Metric,C17630
10K,"R2,R6,R9,R10,R12,R13,R14,R15",R_0805_2012Metric,C17414
1K,"R3,R11",R_0805_2012Metric,C17513
220,"R4,R5",R_0805_2012Metric,C17557
PC817X2CSP9F,U2,SMD-4_L4.6-W6.5-P2.54-LS10.2-TL,C66405
PAM8302AASCR,U3,MSOP-8_L3.0-W3.0-P0.65-LS5.0-BL,C113367

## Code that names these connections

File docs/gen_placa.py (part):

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
# ----------------------------------------------------------------------------
# Heltec V3: zocalos hembra de 18 pines. Pin 1 (GND, pad cuadrado) junto al USB, abajo.
# J3_IZQUIERDA: con la OLED hacia arriba y el USB abajo, J3 (GPIO7...GND) queda a la izquierda. COMPROBAR.
# ----------------------------------------------------------------------------
J3_IZQUIERDA = True
XJ3, XJ2 = (9, 18) if J3_IZQUIERDA else (18, 9)
Y_PIN1 = 25            # fila del pin 1 (el pin p esta en la fila Y_PIN1 + 1 - p)
J3 = ["GND", "3V3", "3V3", "GPIO37", "GPIO46", "GPIO45", "GPIO42", "GPIO41", "GPIO40", "GPIO39", "GPIO38", "GPIO1",
      "GPIO2", "GPIO3", "GPIO4", "GPIO5", "GPIO6", "GPIO7"]
J2 = ["GND", "5V", "Ve", "Ve", "GPIO44", "GPIO43", "RST", "GPIO0", "GPIO36", "GPIO35", "GPIO34", "GPIO33", "GPIO47",
      "GPIO48", "GPIO26", "GPIO21", "GPIO20", "GPIO19"]
# Borde de la placa de la Heltec (50,2 x 25,5 mm): 0,52 pasos fuera de cada fila de pines y ~0,89 mas alla del pin 18
HELTEC_RECT = (min(XJ3, XJ2) - 0.52, Y_PIN1 + 1 - 18 - 0.89, max(XJ3, XJ2) + 0.52, Y_PIN1 + 0.89 + 0.9)

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    return Y_PIN1 + 1 - pin

# Red de cada pin de la Heltec que se usa (los demas se sueldan al zocalo pero no se conectan)
RED_J3 = {1: "GND", 2: "3V3", 3: "3V3", 7: "SCL", 8: "SDA", 11: "AMP_SD", 13: "KEY_GPIO", 10: "GPS_RX",
          15: "DIT", 16: "DAH", 17: "ADC", 18: "TONO"}
RED_J2 = {1: "GND", 2: "5V", 12: "USB_DET", 13: "GPS_TX", 14: "ENC_DT", 17: "ENC_SW", 18: "ENC_CLK"}

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
# Reservas: huecos para piezas que no se montan de entrada. La placa funciona sin ellas.
#   TRAFO: trafo de aislamiento 600:600 en la entrada del decodificador (quitar los 2 puentes de P10)
#   USB:   divisor 47k/68k del pin 5V a GPIO33 para detectar el USB (soldar R11, R12 y los cables A y B)
RESERVAS = ("TRAFO", "USB")

def activo(cond, montado):
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      (1.22, 13.6, 3.78, 15.4), 4, "punto (pat. 1) abajo a la derecha")
resistencia("R7", "330 Ω", (8, 13), (4, 13), "KEY_GPIO", "KEY_A")
resistencia("R10", "10 kΩ", (8, 12), (4, 12), "KEY_GPIO", "GND")
# Reserva USB: divisor del pin 5V (con USB, 4,94 V -> 2,92 V en GPIO33; sin USB, 0,7 V: el pin 5V no queda a 0)
resistencia("R11", "47 kΩ", (3, 20), (7, 20), "5V", "USB_DET", "reserva: detección de USB", reserva="USB")
resistencia("R12", "68 kΩ", (2, 22), (6, 22), "GND", "USB_DET", "reserva: detección de USB", reserva="USB")

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# Pagina
# ----------------------------------------------------------------------------
NOMBRE_RED = {
    "GND": "masa", "3V3": "3,3 V", "TONO": "GPIO7 (tono)", "VOL_IN": "entrada del volumen",
    "VOL_CUR": "cursor del volumen", "AUD": "audio tras C1", "AUR_T": "auriculares T", "AUR_R": "auriculares R",
    "TN": "TN del jack → amplificador", "AMP_SD": "GPIO38 (SD del amplificador)", "ADC": "GPIO6 (ADC)",
    "BIAS": "polarización 1,65 V", "DEC_IN": "entrada del decodificador", "DEC_CUR": "cursor de RV2",
    "KEY_GPIO": "GPIO2 (KEY)", "KEY_A": "ánodo del PC817", "KEY_C": "colector (emisora)", "KEY_E": "emisor (emisora)",
    "DIT": "GPIO4 (DIT)", "DAH": "GPIO5 (DAH)", "ENC_CLK": "GPIO19 (CLK)", "ENC_SW": "GPIO20 (SW)",
    "ENC_DT": "GPIO48 (DT)", "GPS_TX": "GPIO47 (TX del GPS)", "GPS_RX": "GPIO39 (RX del GPS)", "SCL": "GPIO42 (SCL)", "SDA": "GPIO41 (SDA)",
    "TJ": "punta del jack del decodificador", "SJ": "malla del jack del decodificador", "5V": "5 V (pin 5V, solo con USB)",
    "USB_DET": "GPIO33 (detección de USB)",
}

def quien_en(h):
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<h2>Reservas (la placa funciona sin ellas)</h2>
<ul>
<li><b>Trafo de aislamiento 600:600</b> (solo si hay zumbido por lazo de masa): quitar los dos puentes de P10 y conectar el primario a 1 y 3 y el secundario a 2 y 4. El trafo va en la carcasa.</li>
<li><b>Detección de USB</b> (R11 47 kΩ, R12 68 kΩ, en naranja): soldarlas con el puente de B23 y los cables A (5V) y B (GPIO33). Aparcada: sin USB quedan 0,7 V en GPIO33, poco margen (ver NOTAS). Necesita firmware.</li>
<li><b>C3</b> (10 nF, ADC a masa): por la cara de soldaduras, sobre las patas de D2 (H4 y H7).</li>
</ul>
<h2>Antes de soldar nada</h2>
<ul>
<li><b>Comprueba la orientación de la Heltec</b>: con la OLED hacia arriba y el USB hacia ti, la fila de la izquierda debe ser la de 3V3/GPIO7 (J3) y la de la derecha la de 5V/GPIO19 (J2). Si es al revés, avísame y regenero el plano en espejo.</li>
<li>Cuenta los pasos entre las dos filas de pines: deben ser <b>9</b> (22,86 mm).</li>
<li>Comprueba el orden de pines de tus módulos (KY-040, BME280, GPS, PAM8302A) con las tablas de la página 3.</li>
</ul>
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<div><h2>Primer encendido</h2>
<ul>
<li>Poner la Heltec <b>sin módulos conectados</b>, alimentar por USB y comprobar que arranca la v1.06b.</li>
<li>Medir 3,3 V en el VIN de P5 y P8, y unos 1,65 V en GPIO6 (R4/R5).</li>
<li>Conectar los módulos uno a uno y probar cada función: encoder, palas (TX LIBRE), tono por altavoz y auriculares, KEY (TUNE con el polímetro en P6), BME280 (STATUS), decodificador, GPS.</li>
</ul>
<h2>Cuidados</h2>
<ul>
<li>Los pads vecinos que no se unen se tocan a 2,54 mm: revisar con lupa que no haya estaño entre ellos.</li>
<li>Ningún hilo del lado de la emisora (P6) cerca de masa.</li>
<li>El GPS va siempre alimentado: se duerme por UBX con GPIO39.</li>
</ul></div>
<div><h2>Si cambia algo</h2>
<ul>
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

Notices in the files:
docs/gen_placa.py:
SPDX-License-Identifier: GPL-3.0-or-later
Copyright (C) 2026 EA4ILN. Software libre, sin garantia: ver el archivo LICENSE.
El plano que genera (docs/placa_perforada.pdf) es documentacion: CC BY-NC-SA 4.0 (ver LICENSE-HARDWARE.md).
README.md:
https://img.shields.io/badge/software-GPL--3.0-blue
hardware/chispas.kicad_pcb:
Hardware: CC BY-NC-SA 4.0
